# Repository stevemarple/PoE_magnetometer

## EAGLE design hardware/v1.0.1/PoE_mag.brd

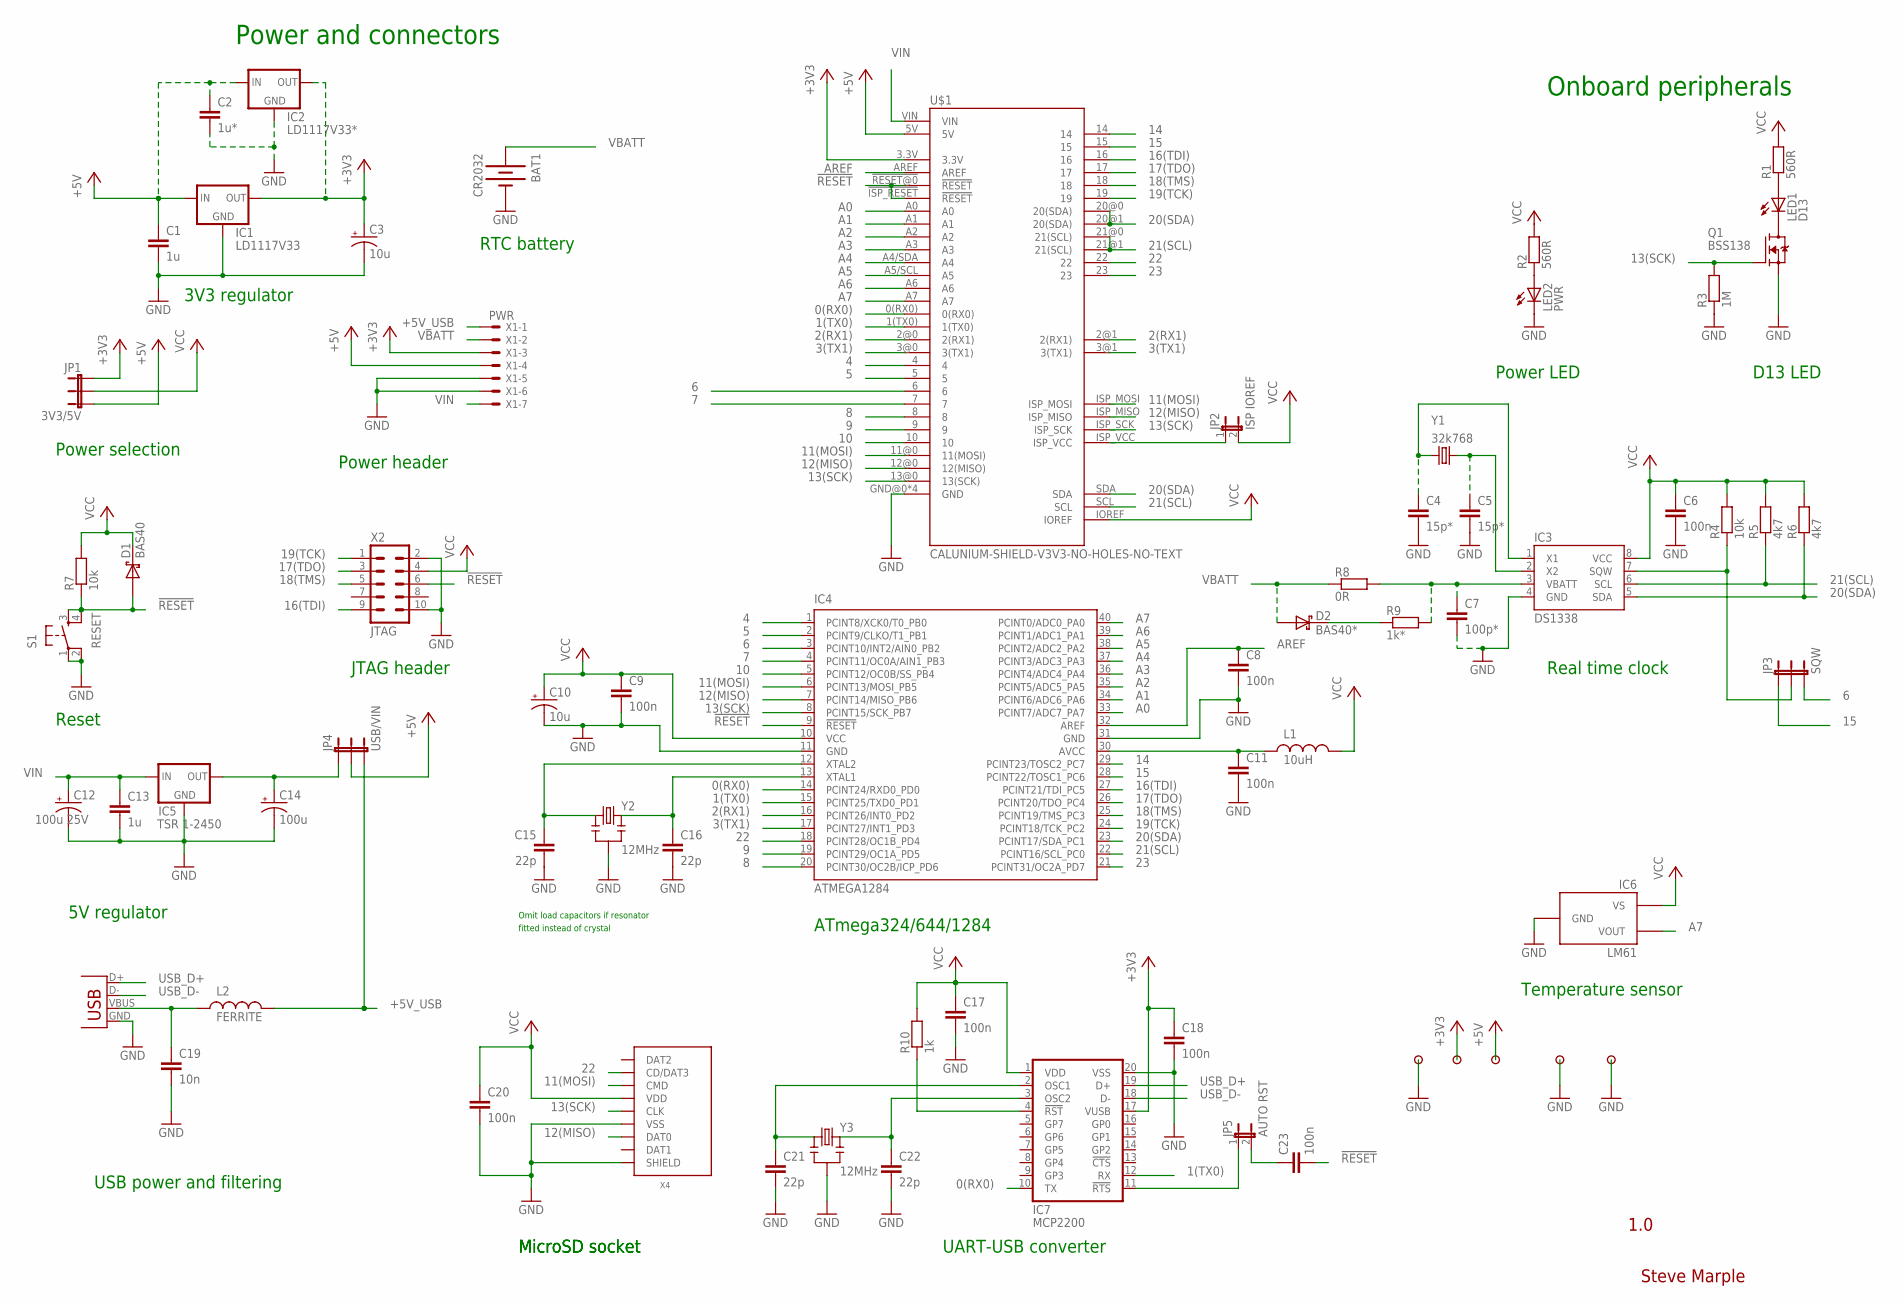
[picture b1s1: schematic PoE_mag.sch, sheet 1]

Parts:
BAT1: CR2032; BATTCOM_20MM_PTH
C1, C13: 1u; 1206-HAND
C2: 1u*; 1206-HAND
C3, C10: 10u; CPOL-RADIAL-10UF-25V
C4, C5: 15p*; 0805-HAND
C6, C8, C9, C11, C17, C18, C20, C23: 100n; 1206-HAND
C7: 100p*; 1206-HAND
C12: 100u 25V; CPOL-RADIAL-100UF-25V-150MIL
C14: 100u; CPOL-RADIAL-100UF-16V
C15, C16, C21, C22: 22p; 0805-HAND
C19: 10n; 1206-HAND
D1: BAS40; SOT23-3-HAND
D2: BAS40*; SOT23-3-HAND
IC1: LD1117V33; SOT223-HAND
IC2: LD1117V33*; TO220
IC3: DS1338; SO08
IC4: ATMEGA1284; DIL40
IC5: TSR 1-2450; TSR-1-XXXX/POWERPAX-P78XX-10
IC6: LM61; SOT23-3-HAND
IC7: MCP2200; SO20
JP1: 3V3/5V; 1X03
JP2: ISP IOREF; 1X02
JP3: SQW; 1X03
JP4: USB/VIN; 1X03
JP5: AUTO RST; 1X02
L1: 10uH; 1210-HAND
L2: FERRITE; 0805-HAND
LED1: D13; LED3MM
LED2: PWR; LED3MM
Q1: BSS138; SOT23-3-HAND
R1, R2: 560R; 1206-HAND
R3: 1M; 1206-HAND
R4, R7: 10k; 1206-HAND
R5, R6: 4k7; 1206-HAND
R8: 0R; 1206-HAND
R9: 1k*; 1206-HAND
R10: 1k; 1206-HAND
S1: RESET; TACTILE-PTH
U$1: CALUNIUM-SHIELD-V3V3-NO-HOLES-NO-TEXT; CALUNIUM-SHIELD-NO-OUTLINE-NO-HOLES-NO-TEXT-V3
U$2, U$3, U$4, U$14, U$15: PAD
X1: PWR; 22-23-2071
X2: JTAG; CON-HARTING-ML10
X3: USB; USB-B-PTH-VERTICAL
X4: MICRO-SD-SOCKETHIROSE-DM3D; MICRO-SD-SOCKET-HIROSE-DM3D
Y1: 32k768; TC38H
Y2, Y3: 12MHz; HC49U-V-RESONATOR

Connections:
0(RX0): IC4.14 (PCINT24/RXD0_PD0), IC7.10 (TX), U$1.0(RX0)
1(TX0): IC4.15 (PCINT25/TXD0_PD1), IC7.12 (RX), U$1.1(TX0)
2(RX1): IC4.16 (PCINT26/INT0_PD2), U$1.2@0 (2(RX1)), U$1.2@1 (2(RX1)); also elsewhere on the board
3(TX1): IC4.17 (PCINT27/INT1_PD3), U$1.3@0 (3(TX1)), U$1.3@1 (3(TX1)); also elsewhere on the board
4: IC4.1 (PCINT8/XCK0/T0_PB0), U$1.4
5: IC4.2 (PCINT9/CLKO/T1_PB1), U$1.5
6: IC4.3 (PCINT10/INT2/AIN0_PB2), JP3.3, U$1.6; also elsewhere on the board
7: IC4.4 (PCINT11/OC0A/AIN1_PB3), U$1.7; also elsewhere on the board
8: IC4.20 (PCINT30/OC2B/ICP_PD6), U$1.8; also elsewhere on the board
9: IC4.19 (PCINT29/OC1A_PD5), U$1.9
10: IC4.5 (PCINT12/OC0B/SS_PB4), U$1.10
11(MOSI): IC4.6 (PCINT13/MOSI_PB5), U$1.11@0 (11(MOSI)), U$1.ISP_MOSI, X4.CMD
12(MISO): IC4.7 (PCINT14/MISO_PB6), U$1.12@0 (12(MISO)), U$1.ISP_MISO, X4.DAT0
13(SCK): IC4.8 (PCINT15/SCK_PB7), Q1.1 (G), R3.2, U$1.13@0 (13(SCK)), U$1.ISP_SCK, X4.CLK
14: IC4.29 (PCINT23/TOSC2_PC7), U$1.14
15: IC4.28 (PCINT22/TOSC1_PC6), JP3.1, U$1.15
16(TDI): IC4.27 (PCINT21/TDI_PC5), U$1.16, X2.9 (TDI)
17(TDO): IC4.26 (PCINT20/TDO_PC4), U$1.17, X2.3 (TDO)
18(TMS): IC4.25 (PCINT19/TMS_PC3), U$1.18, X2.5 (TMS)
19(TCK): IC4.24 (PCINT18/TCK_PC2), U$1.19, X2.1 (TCK)
20(SDA): IC3.5 (SDA), IC4.23 (PCINT17/SDA_PC1), R6.1, U$1.20@0 (20(SDA)), U$1.20@1 (20(SDA)), U$1.SDA; also elsewhere on the board
21(SCL): IC3.6 (SCL), IC4.22 (PCINT16/SCL_PC0), R5.1, U$1.21@0 (21(SCL)), U$1.21@1 (21(SCL)), U$1.SCL; also elsewhere on the board
22: IC4.18 (PCINT28/OC1B_PD4), U$1.22, X4.CD/DAT3
23: IC4.21 (PCINT31/OC2A_PD7), U$1.23
!MCP2200_RESET: IC7.4 (!RST), R10.1
!RESET: C23.2, D1.1 (A), IC4.9 (!RESET), R7.1, S1.3, S1.4, U$1.!ISP_RESET (!RESET), U$1.!RESET@0 (!RESET), X2.6 (!SRST)
+3V3: C3.1 (+), C18.1, IC1.2 (OUT), IC1.4 (OUT), IC2.2 (OUT), IC7.17 (VUSB), JP1.1, U$1.3.3V, U$3.1, X1.3; also elsewhere on the board
+5V: C1.1, C2.1, IC1.3 (IN), IC2.3 (IN), JP1.3, JP4.2, U$1.5V, U$4.1, X1.4; also elsewhere on the board
+5V_USB: JP4.3, L2.2, X1.1
A0: IC4.33 (PCINT7/ADC7_PA7), U$1.A0; also elsewhere on the board
A1: IC4.34 (PCINT6/ADC6_PA6), U$1.A1
A2: IC4.35 (PCINT5/ADC5_PA5), U$1.A2; also elsewhere on the board
A3: IC4.36 (PCINT4/ADC4_PA4), U$1.A3
A4: IC4.37 (PCINT3/ADC3_PA3), U$1.A4/SDA (A4)
A5: IC4.38 (PCINT2/ADC2_PA2), U$1.A5/SCL (A5)
A6: IC4.39 (PCINT1/ADC1_PA1), U$1.A6
A7: IC4.40 (PCINT0/ADC0_PA0), IC6.2 (VOUT), U$1.A7
AREF: C8.1, IC4.32 (AREF), U$1.AREF
AUTO_RESET: IC7.11 (!RTS), JP5.1
AVCC: C11.1, IC4.30 (AVCC), L1.1
GND: BAT1.2 (-), C1.2, C2.2, C3.2 (-), C4.2, C5.2, C6.2, C7.2, C8.2, C9.2, C10.2 (-), C11.2, C12.2 (-), C13.2, C14.2 (-), C15.2, C16.2, C17.2, C18.2, C19.2, C20.2, C21.2, C22.2, IC1.1 (GND), IC2.1 (GND), IC3.4 (GND), IC4.11 (GND), IC4.31 (GND), IC5.2@A (GND), IC5.2@B (GND), IC6.3 (GND), IC7.20 (VSS), LED2.K (C), Q1.2 (S), R3.1, S1.1, S1.2, U$1.GND@0 (GND), U$1.GND@1 (GND), U$1.GND@2 (GND), U$1.GND@3 (GND), U$2.1, U$14.1, U$15.1, X1.5, X1.6, X2.2 (GND), X2.10 (GND), X3.GND, X4.GND (VSS), X4.SHIELD@0 (SHIELD), Y2.GND (2), Y3.GND (2); also elsewhere on the board
unnamed: C16.1, IC4.13 (XTAL1), Y2.2 (3)
unnamed: C15.1, IC4.12 (XTAL2), Y2.1
unnamed: LED1.A, R1.1
unnamed: LED1.K (C), Q1.3 (D)
unnamed: C4.1, IC3.1 (X1), Y1.2
unnamed: JP2.1, U$1.ISP_VCC
unnamed: C22.1, IC7.3 (OSC2), Y3.2 (3)
unnamed: LED2.A, R2.1
unnamed: D2.3 (C), R9.1
unnamed: C7.1, IC3.3 (VBATT), R8.2, R9.2
unnamed: C5.1, IC3.2 (X2), Y1.1
unnamed: C14.1 (+), IC5.3@A (OUT), IC5.3@B (OUT), JP4.1
unnamed: C23.1, JP5.2
unnamed: C21.1, IC7.2 (OSC1), Y3.1
SQW: IC3.7 (SQW), JP3.2, R4.1
USB_D+: IC7.19 (D+), X3.D+
USB_D-: IC7.18 (D-), X3.D-
VBATT: BAT1.1 (+), D2.1 (A), R8.1, X1.2; also elsewhere on the board
VBUS: C19.1, L2.1, X3.VBUS
VCC: C6.1, C9.1, C10.1 (+), C17.1, C20.1, D1.3 (C), IC3.8 (VCC), IC4.10 (VCC), IC6.1 (VS), IC7.1 (VDD), JP1.2, JP2.2, L1.2, R1.2, R2.2, R4.2, R5.2, R6.2, R7.2, R10.2, U$1.IOREF, X2.4 (VTREF), X4.VDD; also elsewhere on the board
VIN: C12.1 (+), C13.1, IC5.1@A (IN), IC5.1@B (IN), U$1.VIN, X1.7; also elsewhere on the board

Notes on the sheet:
Power and connectors
Onboard peripherals
Real time clock
Temperature sensor
ATmega324/644/1284
USB power and filtering
JTAG header
D13 LED
Reset
Power selection
Power header
3V3 regulator
RTC battery
Power LED
Steve Marple
1.0
5V regulator
Omit load capacitors if resonator
fitted instead of crystal
MicroSD socket
UART-USB converter

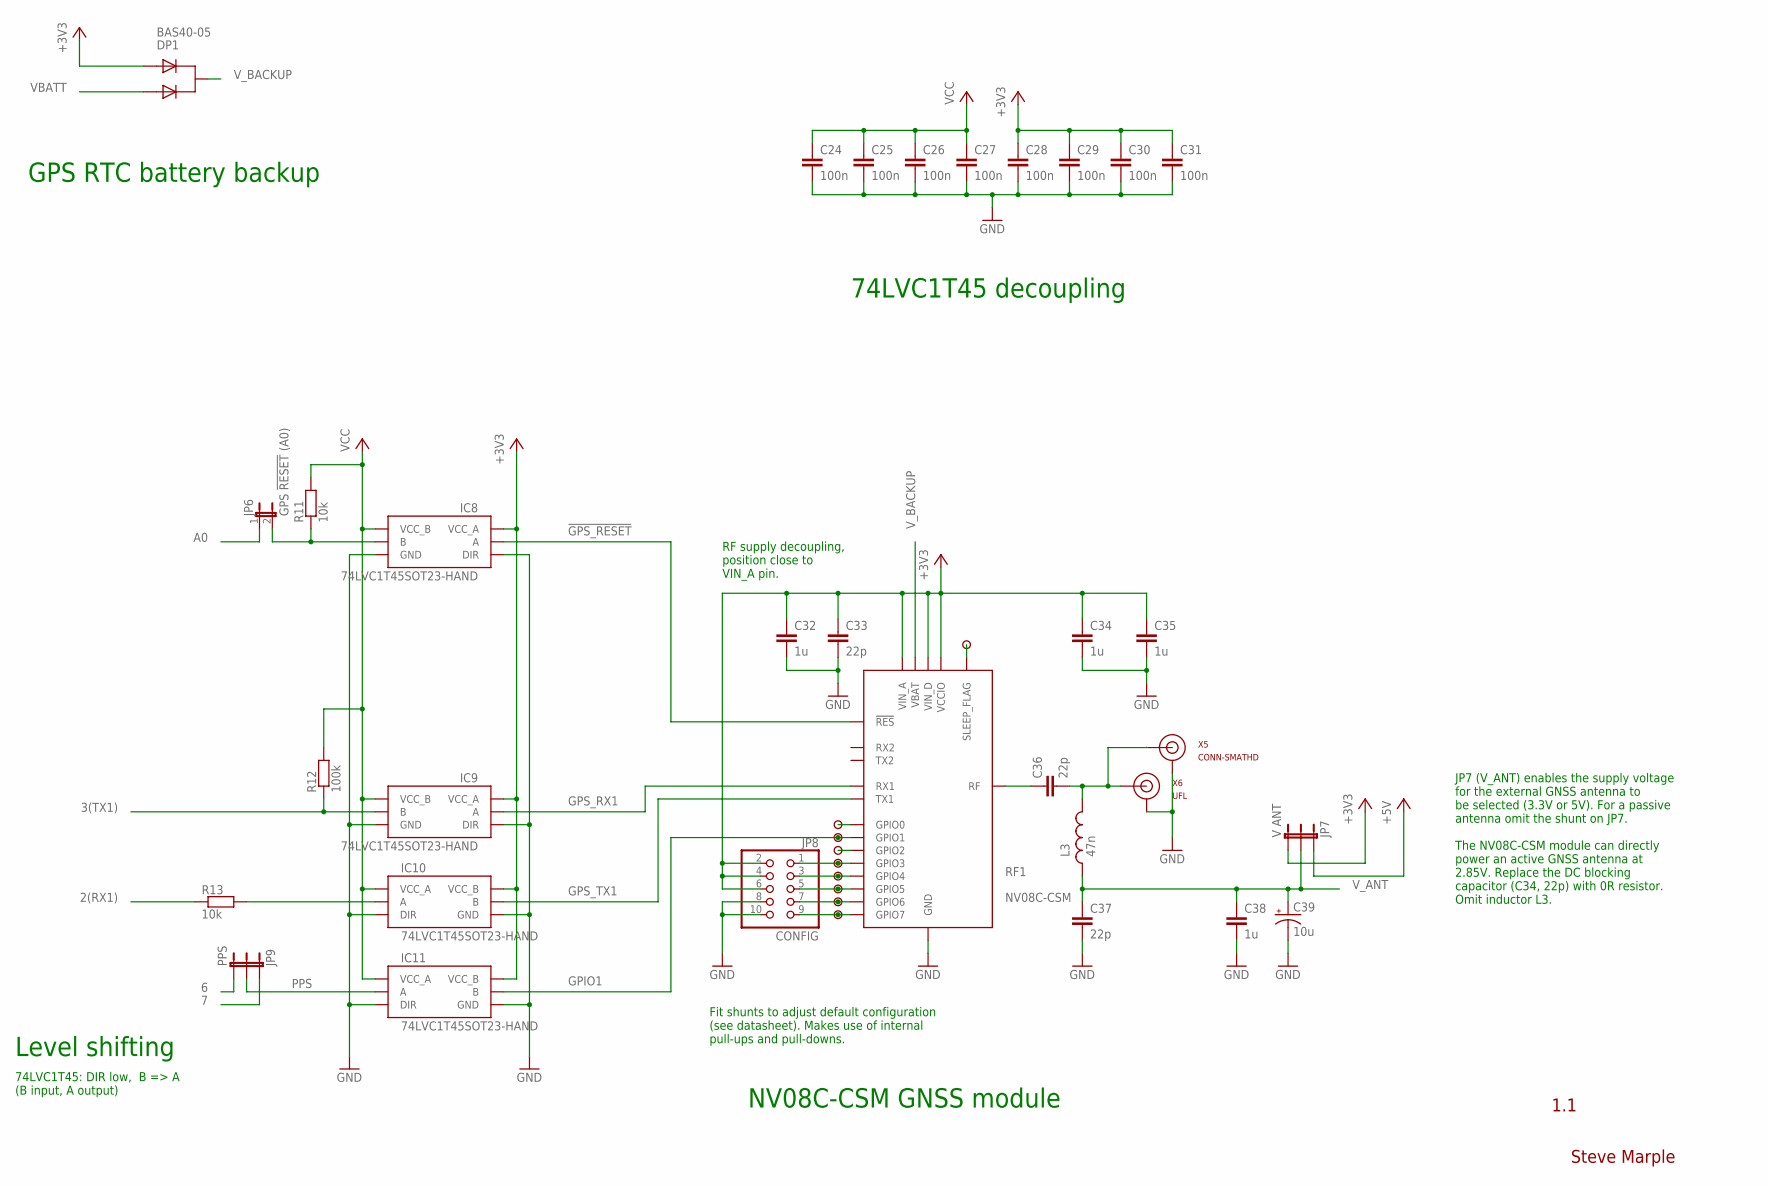
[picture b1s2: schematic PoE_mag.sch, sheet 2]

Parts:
C24, C25, C26, C27, C28, C29, C30, C31: 100n; 1206-HAND
C32, C34, C35, C38: 1u; 1206-HAND
C33, C36, C37: 22p; 0805-HAND
C39: 10u; CPOL-RADIAL-10UF-25V
DP1: BAS40-05; SOT23-3-HAND
IC8, IC9, IC10, IC11: 74LVC1T45SOT23-HAND; SOT23-6-HAND
JP6: GPS !RESET! (A0); 1X02
JP7: V ANT; 1X03
JP8: CONFIG; 2X05
JP9: PPS; 1X03
L3: 47n; 0805-HAND
R11, R13: 10k; 1206-HAND
R12: 100k; 1206-HAND
RF1: NV08C-CSM; NVC08C-CSM-HAND
U$5, U$6, U$7, U$9, U$10, U$11, U$12, U$13: PAD
U$8: ?; PAD
X5: CONN-SMATHD; SMA-THD
X6: UFL; CONN-UFL-HAND-SOLDERING

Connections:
2(RX1): R13.1; also elsewhere on the board
3(TX1): IC9.4 (B), R12.1; also elsewhere on the board
6: JP9.3; also elsewhere on the board
7: JP9.1; also elsewhere on the board
!GPS_RESET: IC8.3 (A), RF1.P$25 (!RES)
+3V3: C28.1, C29.1, C30.1, C31.1, C32.1, C33.1, C34.1, C35.1, DP1.2 (A2), IC8.1 (VCC_A), IC9.1 (VCC_A), IC10.6 (VCC_B), IC11.6 (VCC_B), JP7.3, JP8.2, JP8.4, JP8.6, RF1.P$8 (VIN_A), RF1.P$26 (VIN_D), RF1.P$28 (VCCIO); also elsewhere on the board
+5V: JP7.1; also elsewhere on the board
A0: JP6.1; also elsewhere on the board
GND: C24.2, C25.2, C26.2, C27.2, C28.2, C29.2, C30.2, C31.2, C32.2, C33.2, C34.2, C35.2, C37.2, C38.2, C39.2 (-), IC8.2 (GND), IC8.5 (DIR), IC9.2 (GND), IC9.5 (DIR), IC10.2 (GND), IC10.5 (DIR), IC11.2 (GND), IC11.5 (DIR), JP8.8, JP8.10, RF1.P$3 (GND), RF1.P$9 (GND), RF1.P$10 (GND), RF1.P$11 (GND), RF1.P$12 (GND), RF1.P$13 (GND), RF1.P$14 (GND), RF1.P$16 (GND), RF1.P$17 (GND), RF1.P$18 (GND), RF1.P$19 (GND), RF1.P$22 (GND), RF1.P$24 (GND), RF1.P$27 (GND), RF1.P$29 (GND), RF1.P$34 (GND), X5.GND@0 (GND), X5.GND@1 (GND), X5.GND@2 (GND), X5.GND@3 (GND), X6.GND@0 (GND), X6.GND@1 (GND); also elsewhere on the board
GPIO0: RF1.P$20 (GPIO0), U$6.1
GPIO1: IC11.4 (B), RF1.P$2 (GPIO1), U$7.1
GPIO2: RF1.P$1 (GPIO2), U$8.1
GPIO3: JP8.1, RF1.P$6 (GPIO3), U$9.1
GPIO4: JP8.3, RF1.P$7 (GPIO4), U$10.1
GPIO5: JP8.5, RF1.P$4 (GPIO5), U$11.1
GPIO6: JP8.7, RF1.P$35 (GPIO6), U$12.1
GPIO7: JP8.9, RF1.P$5 (GPIO7), U$13.1
GPS_RX1: IC9.3 (A), RF1.P$33 (RX1)
GPS_TX1: IC10.4 (B), RF1.P$32 (TX1)
unnamed: IC8.4 (B), JP6.2, R11.1
unnamed: C36.2, L3.2, X5.SIG (SIGNAL), X6.SIGNAL
unnamed: C36.1, RF1.P$15 (RF)
unnamed: IC10.3 (A), R13.2
PPS: IC11.3 (A), JP9.2
SLEEP_FLAG: RF1.P$21 (SLEEP_FLAG), U$5.1
VBATT: DP1.1 (A1); also elsewhere on the board
VCC: C24.1, C25.1, C26.1, C27.1, IC8.6 (VCC_B), IC9.6 (VCC_B), IC10.1 (VCC_A), IC11.1 (VCC_A), R11.2, R12.2; also elsewhere on the board
V_ANT: C37.1, C38.1, C39.1 (+), JP7.2, L3.1
V_BACKUP: DP1.3 (C), RF1.P$23 (VBAT)

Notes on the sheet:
1.1
Steve Marple
Level shifting
GPS RTC battery backup
74LVC1T45: DIR low, B => A (B input, A output)
RF supply decoupling, position close to VIN_A pin.
Fit shunts to adjust default configuration (see datasheet). Makes use of internal pull-ups and pull-downs.
74LVC1T45 decoupling
NV08C-CSM GNSS module
JP7 (V_ANT) enables the supply voltage for the external GNSS antenna to be selected (3.3V or 5V). For a passive antenna omit the shunt on JP7. The NV08C-CSM module can directly power an active GNSS antenna at 2.85V. Replace the DC blocking capacitor (C34, 22p) with 0R resistor. Omit inductor L3.

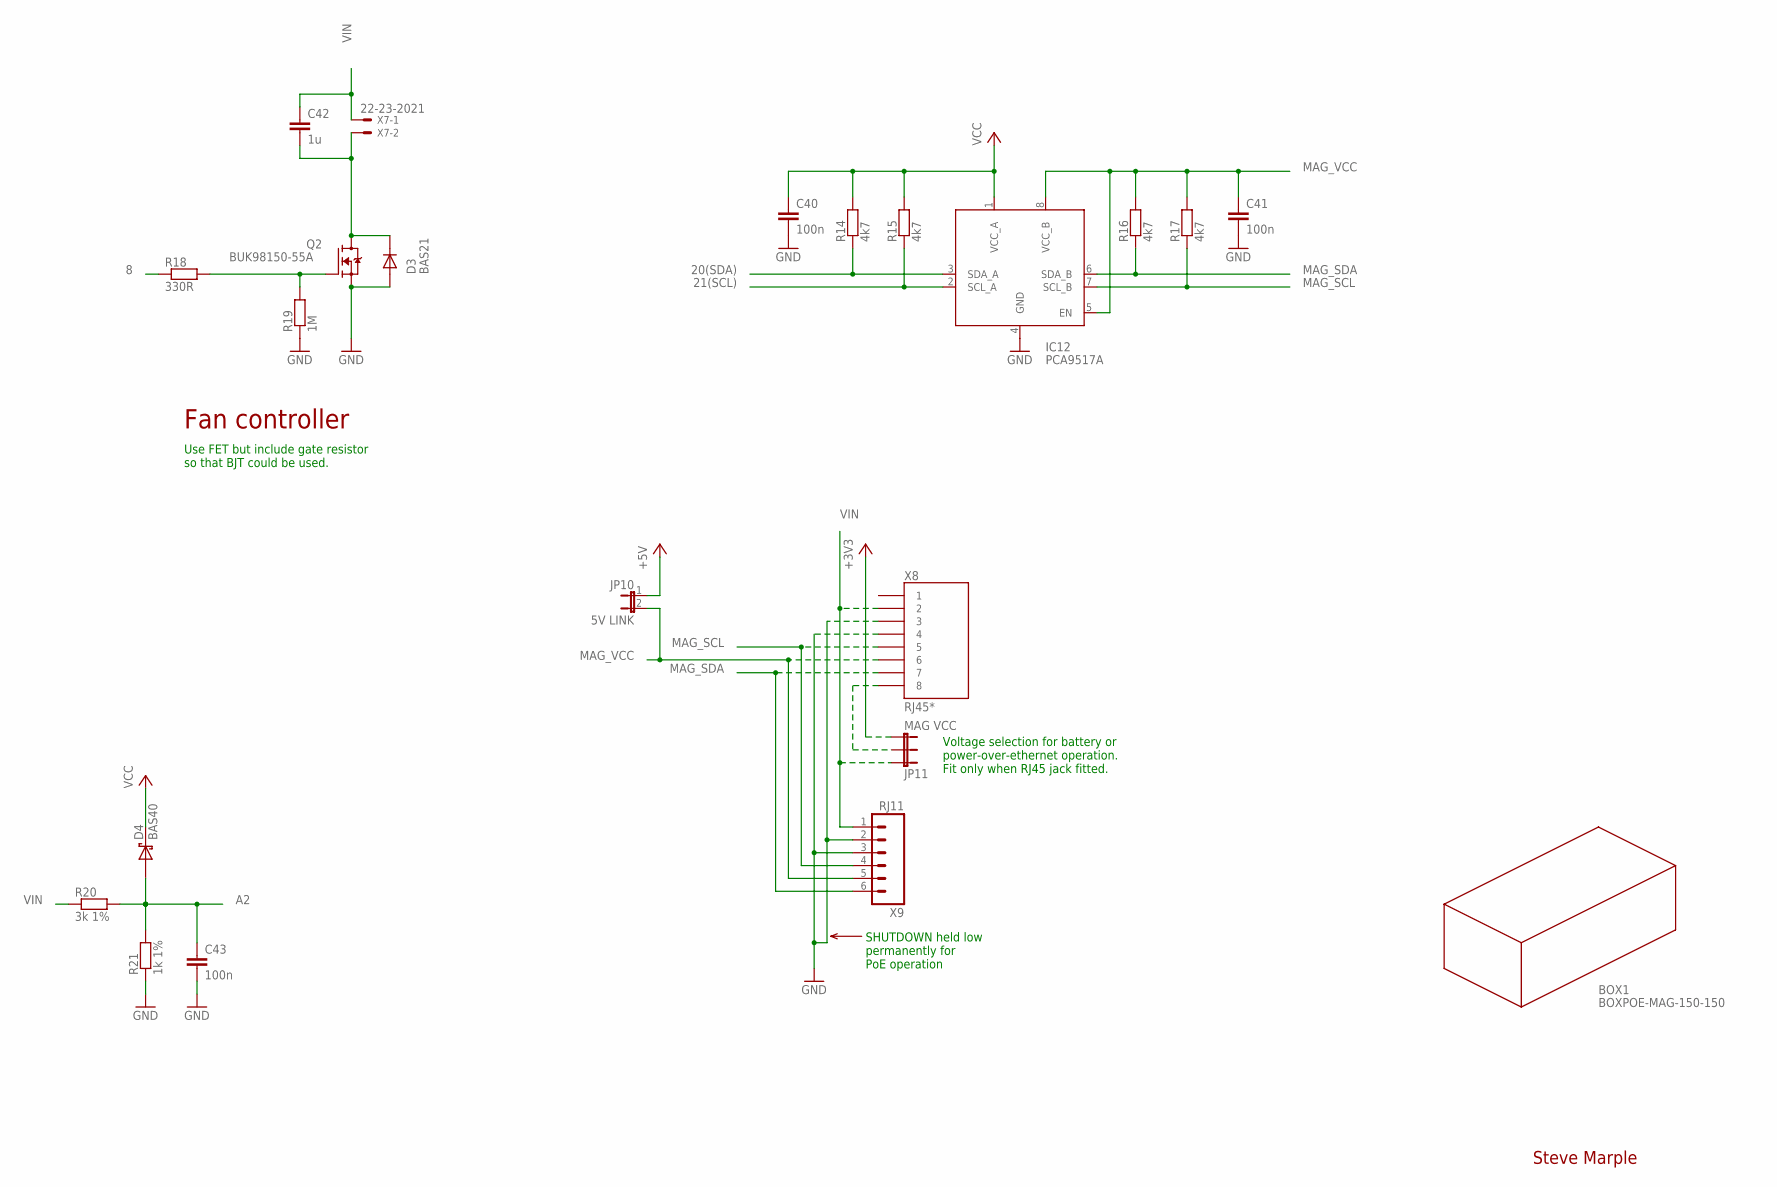
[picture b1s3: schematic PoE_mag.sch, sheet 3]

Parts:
BOX1: BOXPOE-MAG-150-150; FIBOX-PC-M-95-G-POE-MAG
C40, C41, C43: 100n; 1206-HAND
C42: 1u; 1206-HAND
D3: BAS21; SOT23-3-HAND
D4: BAS40; SOT23-3-HAND
IC12: PCA9517A; SO08
JP10: 5V LINK; 1X02
JP11: MAG VCC; 1X03
Q2: BUK98150-55A; SOT223-HAND
R14, R15, R16, R17: 4k7; 1206-HAND
R18: 330R; 1206-HAND
R19: 1M; 1206-HAND
R20: 3k 1%; 1206-HAND
R21: 1k 1%; 1206-HAND
X7: 22-23-2021
X8: RJ45*; RJ45-8
X9: RJ11; RJ11-6

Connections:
8: R18.1; also elsewhere on the board
20(SDA): IC12.3 (SDA_A), R14.1; also elsewhere on the board
21(SCL): IC12.2 (SCL_A), R15.1; also elsewhere on the board
+3V3: JP11.3; also elsewhere on the board
+5V: JP10.1; also elsewhere on the board
A2: C43.1, D4.1 (A), R20.2, R21.2; also elsewhere on the board
FAN_CTRL: C42.2, D3.3 (C), Q2.2 (D), Q2.4 (D), X7.2
GND: C40.2, C41.2, C43.2, D3.1 (A), IC12.4 (GND), Q2.3 (S), R19.1, R21.1, X8.3, X8.4, X9.2, X9.3; also elsewhere on the board
MAG_SCL: IC12.7 (SCL_B), R17.1, X8.5, X9.4
MAG_SDA: IC12.6 (SDA_B), R16.1, X8.7, X9.6
MAG_VCC: C41.1, IC12.5 (EN), IC12.8 (VCC_B), JP10.2, R16.2, R17.2, X8.6, X9.5
unnamed: JP11.2, X8.8
unnamed: Q2.1 (G), R18.2, R19.2
VCC: C40.1, D4.3 (C), IC12.1 (VCC_A), R14.2, R15.2; also elsewhere on the board
VIN: C42.1, JP11.1, R20.1, X7.1, X8.2, X9.1; also elsewhere on the board

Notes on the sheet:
Fan controller
Use FET but include gate resistor so that BJT could be used.
Voltage selection for battery or power-over-ethernet operation. Fit only when RJ45 jack fitted.
SHUTDOWN held low permanently for PoE operation
Steve Marple

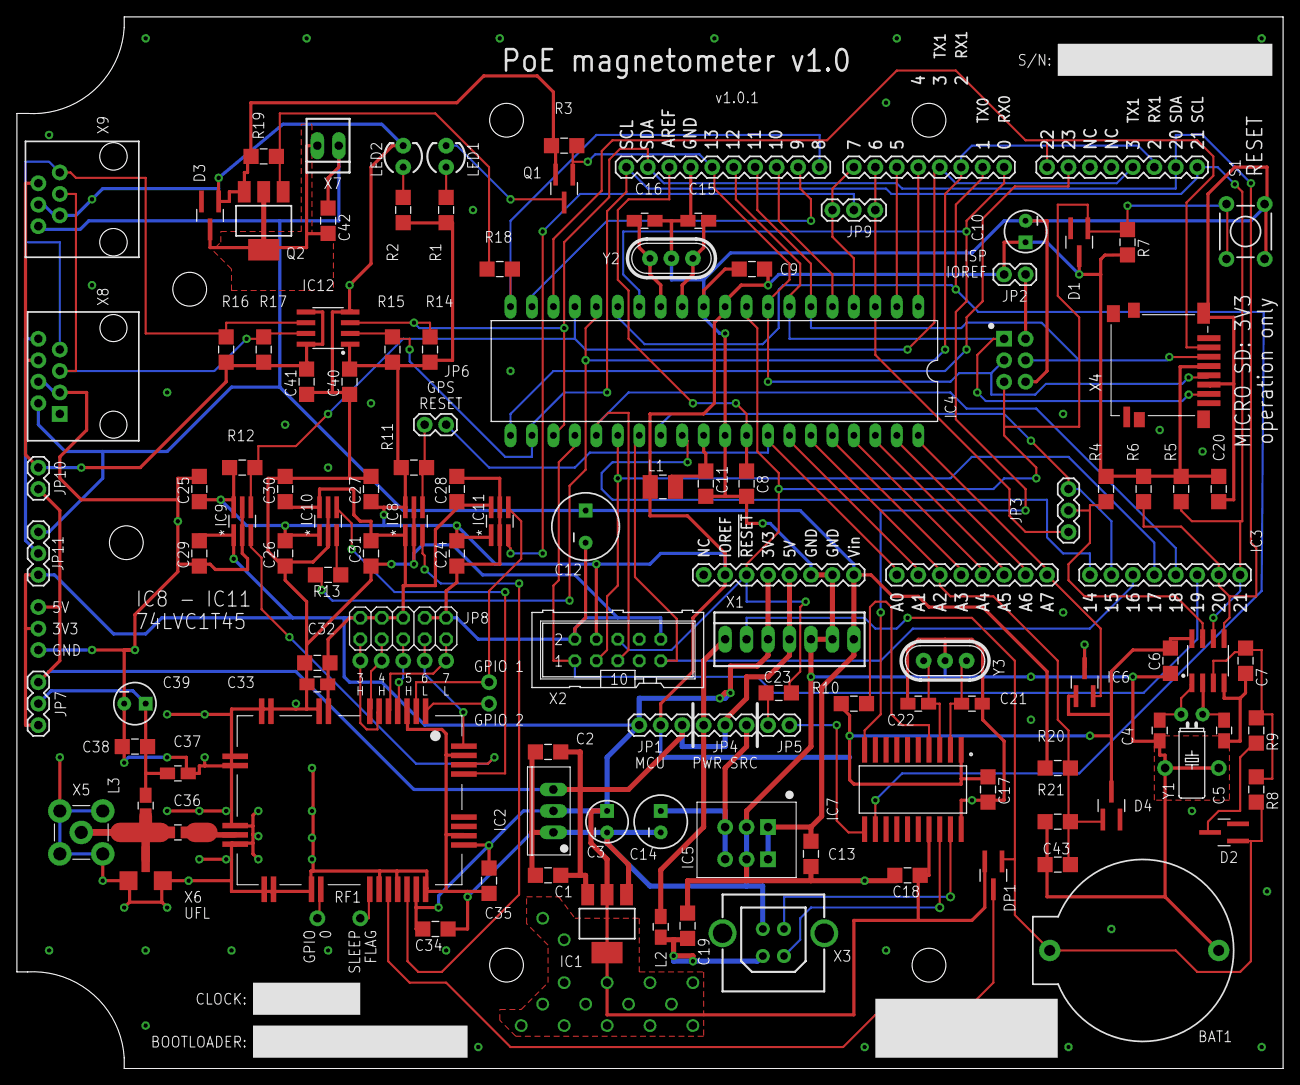
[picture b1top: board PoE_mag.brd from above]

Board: 2 copper layers, 149.9 x 124.5 mm, 130 parts (0 on the bottom side), 87 nets.

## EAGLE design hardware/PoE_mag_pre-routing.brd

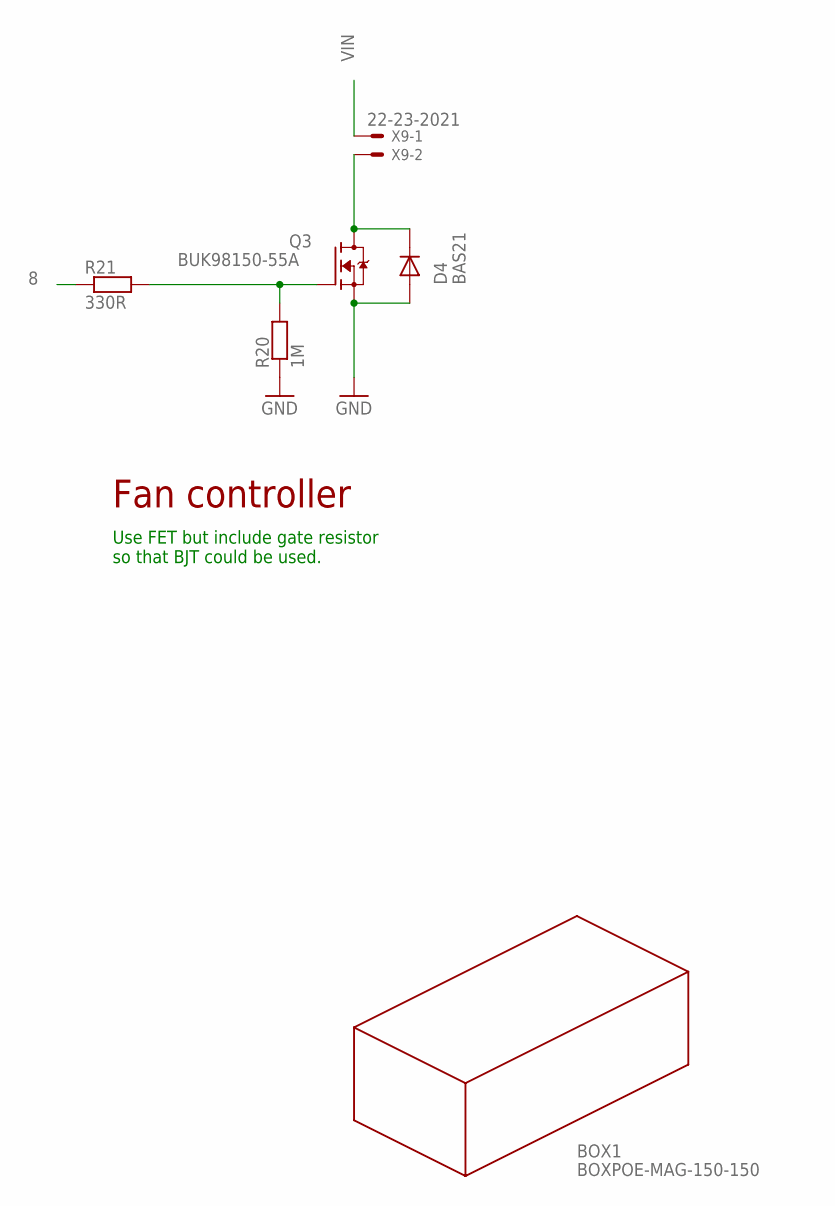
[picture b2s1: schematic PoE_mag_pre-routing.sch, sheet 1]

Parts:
BOX1: BOXPOE-MAG-150-150; FIBOX-PC-M-95-G-POE-MAG
D4: BAS21; SOT23-3-HAND
Q3: BUK98150-55A; SOT223-HAND
R20: 1M; 1206-HAND
R21: 330R; 1206-HAND
X9: 22-23-2021

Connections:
8: R21.1; also elsewhere on the board
FAN_CTRL: D4.3 (C), Q3.2 (D), Q3.4 (D), X9.2
GND: D4.1 (A), Q3.3 (S), R20.1; also elsewhere on the board
unnamed: Q3.1 (G), R20.2, R21.2
VIN: X9.1; also elsewhere on the board

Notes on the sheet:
Fan controller
Use FET but include gate resistor so that BJT could be used.

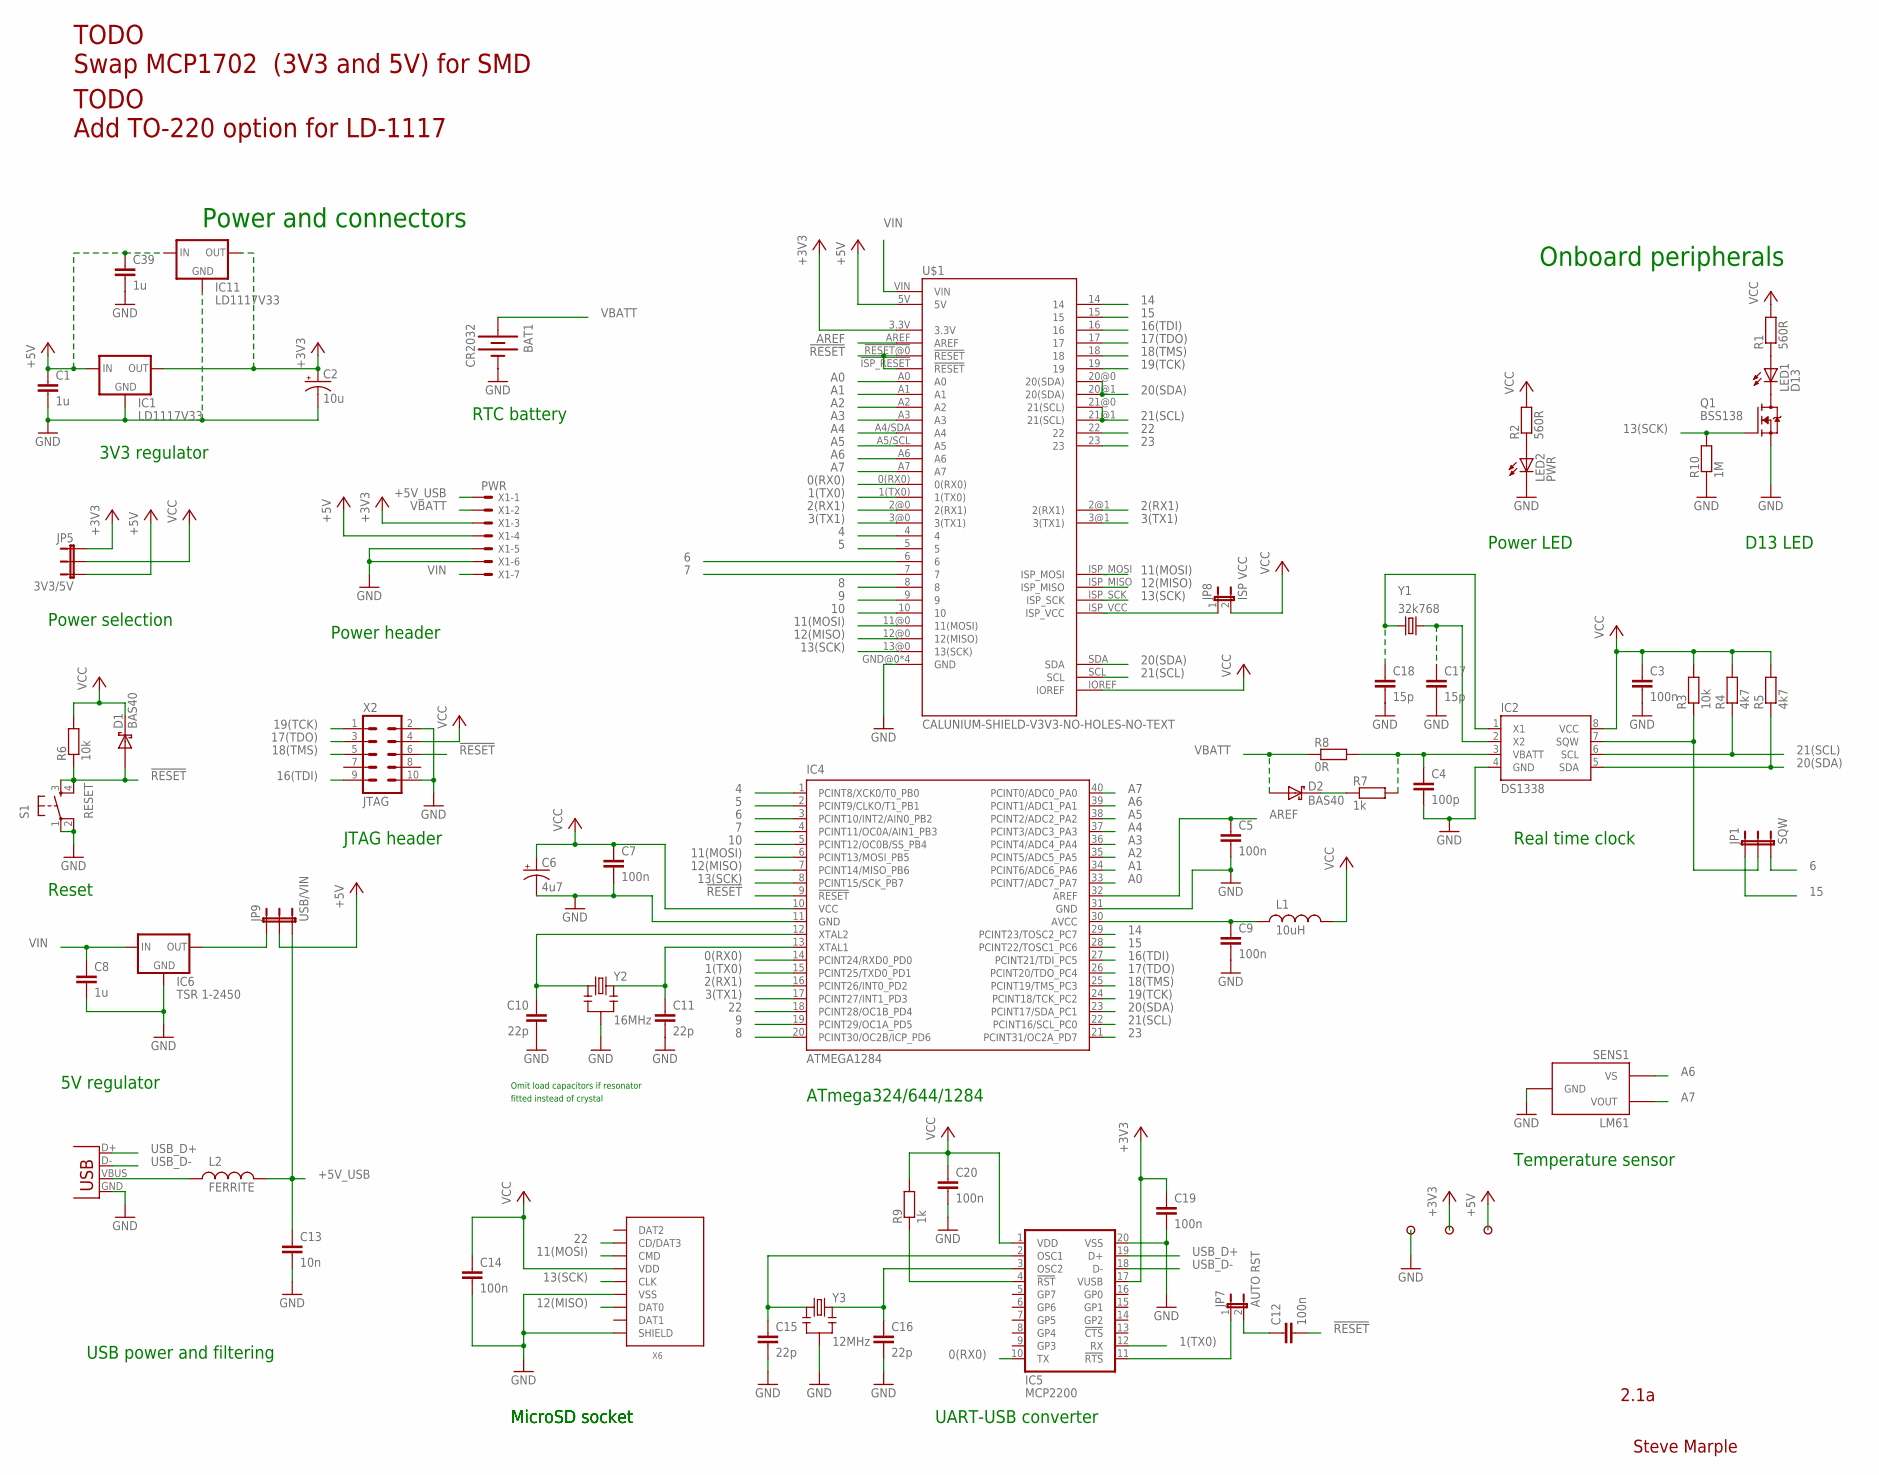
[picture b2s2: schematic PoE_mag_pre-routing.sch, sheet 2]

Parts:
BAT1: CR2032; BATTCOM_20MM_PTH
C1, C8, C39: 1u; 1206-HAND
C2: 10u; CPOL-RADIAL-10UF-25V
C3, C5, C7, C9, C12, C14, C19, C20: 100n; 1206-HAND
C4: 100p; 1206-HAND
C6: 4u7; CPOL-RADIAL-10UF-25V
C10, C11, C15, C16: 22p; 0805-HAND
C13: 10n; 1206-HAND
C17, C18: 15p; 0805-HAND
D1, D2: BAS40; SOT23-3-HAND
IC1: LD1117V33; TO220
IC2: DS1338; SO08
IC4: ATMEGA1284; DIL40
IC5: MCP2200; SO20
IC6: TSR 1-2450; TSR-1-XXXX/POWERPAX-P78XX-10
IC11: LD1117V33; SOT223-HAND
JP1: SQW; 1X03
JP5: 3V3/5V; 1X03
JP7: AUTO RST; 1X02
JP8: ISP VCC; 1X02
JP9: USB/VIN; 1X03
L1: 10uH; 1210-HAND
L2: FERRITE; 0805-HAND
LED1: D13; LED3MM
LED2: PWR; LED3MM
Q1: BSS138; SOT23-3-HAND
R1, R2: 560R; 1206-HAND
R3, R6: 10k; 1206-HAND
R4, R5: 4k7; 1206-HAND
R7, R9: 1k; 1206-HAND
R8: 0R; 1206-HAND
R10: 1M; 1206-HAND
S1: RESET; TACTILE-PTH
SENS1: LM61; TO-92
U$1: CALUNIUM-SHIELD-V3V3-NO-HOLES-NO-TEXT; CALUNIUM-SHIELD-NO-OUTLINE-NO-HOLES-NO-TEXT-V3
U$11, U$12, U$13: PAD
X1: PWR; 22-23-2071
X2: JTAG; CON-HARTING-ML10
X3: USB; USB-B-PTH-VERTICAL
X6: MICRO-SD-SOCKETHIROSE-DM3D; MICRO-SD-SOCKET-HIROSE-DM3D
Y1: 32k768; TC38H
Y2: 16MHz; HC49U-V-RESONATOR
Y3: 12MHz; HC49U-V-RESONATOR

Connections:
0(RX0): IC4.14 (PCINT24/RXD0_PD0), IC5.10 (TX), U$1.0(RX0)
1(TX0): IC4.15 (PCINT25/TXD0_PD1), IC5.12 (RX), U$1.1(TX0)
2(RX1): IC4.16 (PCINT26/INT0_PD2), U$1.2@0 (2(RX1)), U$1.2@1 (2(RX1)); also elsewhere on the board
3(TX1): IC4.17 (PCINT27/INT1_PD3), U$1.3@0 (3(TX1)), U$1.3@1 (3(TX1)); also elsewhere on the board
4: IC4.1 (PCINT8/XCK0/T0_PB0), U$1.4
5: IC4.2 (PCINT9/CLKO/T1_PB1), U$1.5
6: IC4.3 (PCINT10/INT2/AIN0_PB2), JP1.3, U$1.6; also elsewhere on the board
7: IC4.4 (PCINT11/OC0A/AIN1_PB3), U$1.7; also elsewhere on the board
8: IC4.20 (PCINT30/OC2B/ICP_PD6), U$1.8; also elsewhere on the board
9: IC4.19 (PCINT29/OC1A_PD5), U$1.9
10: IC4.5 (PCINT12/OC0B/SS_PB4), U$1.10
11(MOSI): IC4.6 (PCINT13/MOSI_PB5), U$1.11@0 (11(MOSI)), U$1.ISP_MOSI, X6.CMD
12(MISO): IC4.7 (PCINT14/MISO_PB6), U$1.12@0 (12(MISO)), U$1.ISP_MISO, X6.DAT0
13(SCK): IC4.8 (PCINT15/SCK_PB7), Q1.1 (G), R10.2, U$1.13@0 (13(SCK)), U$1.ISP_SCK, X6.CLK
14: IC4.29 (PCINT23/TOSC2_PC7), U$1.14
15: IC4.28 (PCINT22/TOSC1_PC6), JP1.1, U$1.15
16(TDI): IC4.27 (PCINT21/TDI_PC5), U$1.16, X2.9 (TDI)
17(TDO): IC4.26 (PCINT20/TDO_PC4), U$1.17, X2.3 (TDO)
18(TMS): IC4.25 (PCINT19/TMS_PC3), U$1.18, X2.5 (TMS)
19(TCK): IC4.24 (PCINT18/TCK_PC2), U$1.19, X2.1 (TCK)
20(SDA): IC2.5 (SDA), IC4.23 (PCINT17/SDA_PC1), R5.1, U$1.20@0 (20(SDA)), U$1.20@1 (20(SDA)), U$1.SDA; also elsewhere on the board
21(SCL): IC2.6 (SCL), IC4.22 (PCINT16/SCL_PC0), R4.1, U$1.21@0 (21(SCL)), U$1.21@1 (21(SCL)), U$1.SCL; also elsewhere on the board
22: IC4.18 (PCINT28/OC1B_PD4), U$1.22, X6.CD/DAT3
23: IC4.21 (PCINT31/OC2A_PD7), U$1.23
!MCP2200_RESET: IC5.4 (!RST), R9.1
!RESET: C12.2, D1.1 (A), IC4.9 (!RESET), R6.1, S1.3, S1.4, U$1.!ISP_RESET (!RESET), U$1.!RESET@0 (!RESET), X2.6 (!SRST)
+3V3: C2.1 (+), C19.1, IC1.2 (OUT), IC5.17 (VUSB), IC11.2 (OUT), IC11.4 (OUT), JP5.1, U$1.3.3V, U$11.1, X1.3; also elsewhere on the board
+5V: C1.1, C39.1, IC1.3 (IN), IC11.3 (IN), JP5.3, JP9.2, U$1.5V, U$12.1, X1.4; also elsewhere on the board
+5V_USB: C13.1, JP9.3, L2.2, X1.1
A0: IC4.33 (PCINT7/ADC7_PA7), U$1.A0; also elsewhere on the board
A1: IC4.34 (PCINT6/ADC6_PA6), U$1.A1
A2: IC4.35 (PCINT5/ADC5_PA5), U$1.A2; also elsewhere on the board
A3: IC4.36 (PCINT4/ADC4_PA4), U$1.A3
A4: IC4.37 (PCINT3/ADC3_PA3), U$1.A4/SDA (A4)
A5: IC4.38 (PCINT2/ADC2_PA2), U$1.A5/SCL (A5)
A6: IC4.39 (PCINT1/ADC1_PA1), SENS1.1 (VS), U$1.A6
A7: IC4.40 (PCINT0/ADC0_PA0), SENS1.2 (VOUT), U$1.A7
AREF: C5.1, IC4.32 (AREF), U$1.AREF
AUTO_RESET: IC5.11 (!RTS), JP7.1
AVCC: C9.1, IC4.30 (AVCC), L1.1
GND: BAT1.2 (-), C1.2, C2.2 (-), C3.2, C4.2, C5.2, C6.2 (-), C7.2, C8.2, C9.2, C10.2, C11.2, C13.2, C14.2, C15.2, C16.2, C17.2, C18.2, C19.2, C20.2, C39.2, IC1.1 (GND), IC2.4 (GND), IC4.11 (GND), IC4.31 (GND), IC5.20 (VSS), IC6.2@A (GND), IC6.2@B (GND), IC11.1 (GND), LED2.K (C), Q1.2 (S), R10.1, S1.1, S1.2, SENS1.3 (GND), U$1.GND@0 (GND), U$1.GND@1 (GND), U$1.GND@2 (GND), U$1.GND@3 (GND), U$13.1, X1.5, X1.6, X2.2 (GND), X2.10 (GND), X3.GND, X6.GND (VSS), X6.SHIELD@0 (SHIELD), Y2.GND (2), Y3.GND (2); also elsewhere on the board
unnamed: C11.1, IC4.13 (XTAL1), Y2.2 (3)
unnamed: C10.1, IC4.12 (XTAL2), Y2.1
unnamed: LED1.A, R1.1
unnamed: LED1.K (C), Q1.3 (D)
unnamed: C18.1, IC2.1 (X1), Y1.2
unnamed: JP8.1, U$1.ISP_VCC
unnamed: C16.1, IC5.3 (OSC2), Y3.2 (3)
unnamed: LED2.A, R2.1
unnamed: D2.3 (C), R7.1
unnamed: C4.1, IC2.3 (VBATT), R7.2, R8.2
unnamed: C17.1, IC2.2 (X2), Y1.1
unnamed: IC6.3@A (OUT), IC6.3@B (OUT), JP9.1
unnamed: C12.1, JP7.2
unnamed: C15.1, IC5.2 (OSC1), Y3.1
SQW: IC2.7 (SQW), JP1.2, R3.1
USB_D+: IC5.19 (D+), X3.D+
USB_D-: IC5.18 (D-), X3.D-
VBATT: BAT1.1 (+), D2.1 (A), R8.1, X1.2; also elsewhere on the board
VBUS: L2.1, X3.VBUS
VCC: C3.1, C6.1 (+), C7.1, C14.1, C20.1, D1.3 (C), IC2.8 (VCC), IC4.10 (VCC), IC5.1 (VDD), JP5.2, JP8.2, L1.2, R1.2, R2.2, R3.2, R4.2, R5.2, R6.2, R9.2, U$1.IOREF, X2.4 (VTREF), X6.VDD; also elsewhere on the board
VIN: C8.1, IC6.1@A (IN), IC6.1@B (IN), U$1.VIN, X1.7; also elsewhere on the board

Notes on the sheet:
Power and connectors
Onboard peripherals
Real time clock
Temperature sensor
ATmega324/644/1284
USB power and filtering
JTAG header
D13 LED
Reset
Power selection
Power header
3V3 regulator
RTC battery
Power LED
Steve Marple
2.1a
5V regulator
Omit load capacitors if resonator
fitted instead of crystal
MicroSD socket
UART-USB converter
TODO Swap MCP1702 (3V3 and 5V) for SMD
TODO Add TO-220 option for LD-1117

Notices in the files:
parts and their libraries:
SparkFun: Licensing: CC v3.0 Share-Alike You are welcome to use this library for commercial purposes.
